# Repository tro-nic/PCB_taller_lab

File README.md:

# PCB_taller_lab
PCB desarrolladas en KICAD y otros, herramientas o dispositvos para el taller y laboratorio

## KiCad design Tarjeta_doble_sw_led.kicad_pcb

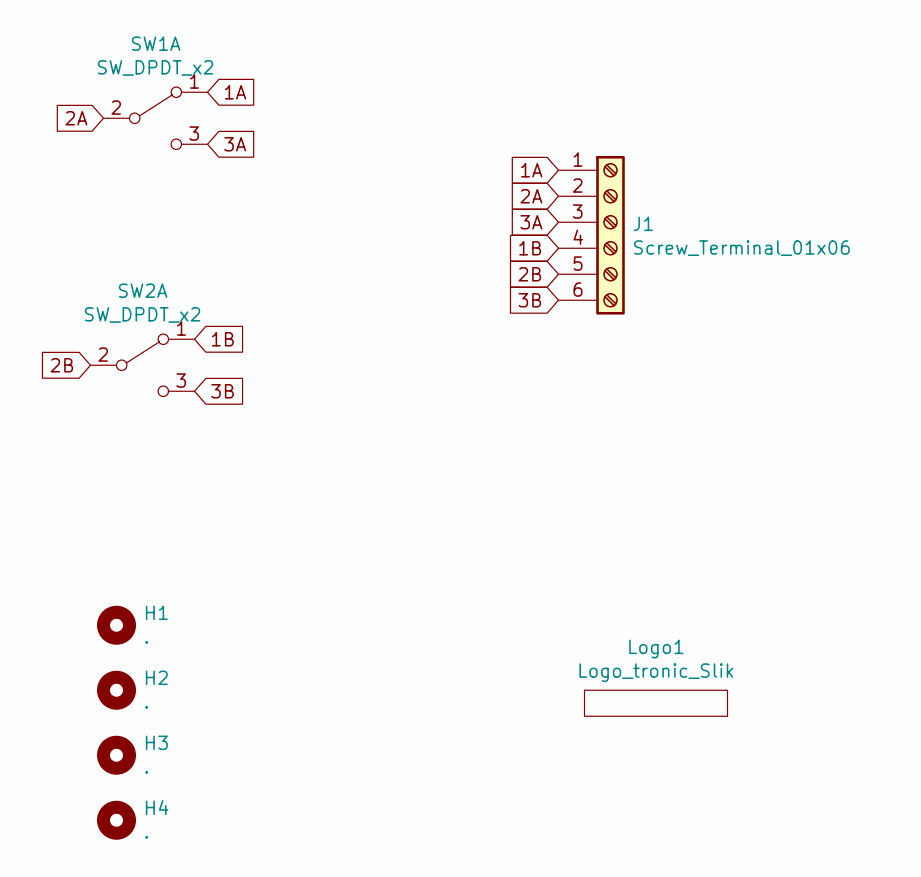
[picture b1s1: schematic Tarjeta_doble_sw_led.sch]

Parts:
H1, H2, H3, H4: .; MountingHole_2.1mm
J1: Screw_Terminal_01x06; TerminalBlock_bornier-6_P5.08mm
Logo1: Logo_tronic_Slik; TRONIC_PCB_B
SW1, SW2: SW_DPDT_x2; TerminalBlock_bornier-3_P5.08mm

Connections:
1A: J1.1, SW1.1 (A)
1B: J1.4, SW2.1 (A)
2A: J1.2, SW1.2 (B)
2B: J1.5, SW2.2 (B)
3A: J1.3, SW1.3 (C)
3B: J1.6, SW2.3 (C)

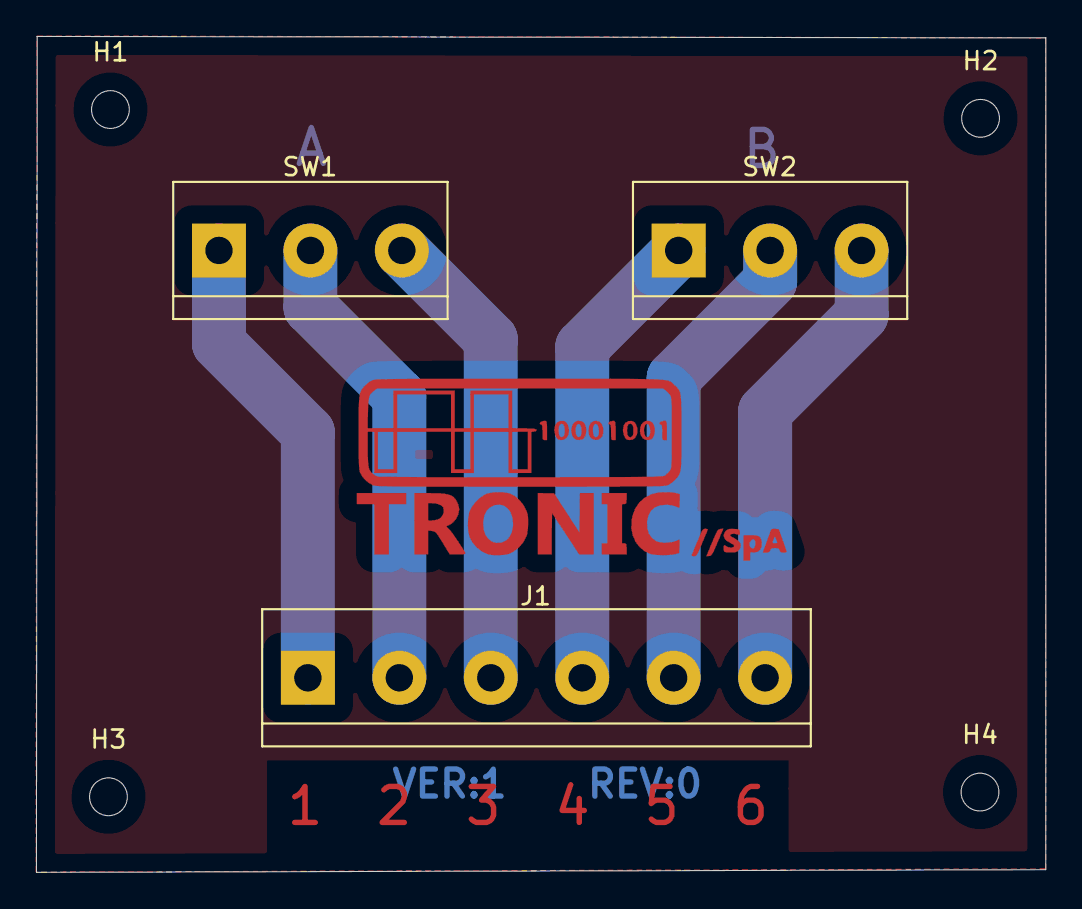
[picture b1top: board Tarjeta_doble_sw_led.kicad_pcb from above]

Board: 2 copper layers, 56.1 x 46.4 mm, 8 parts (0 on the bottom side), 6 nets.
